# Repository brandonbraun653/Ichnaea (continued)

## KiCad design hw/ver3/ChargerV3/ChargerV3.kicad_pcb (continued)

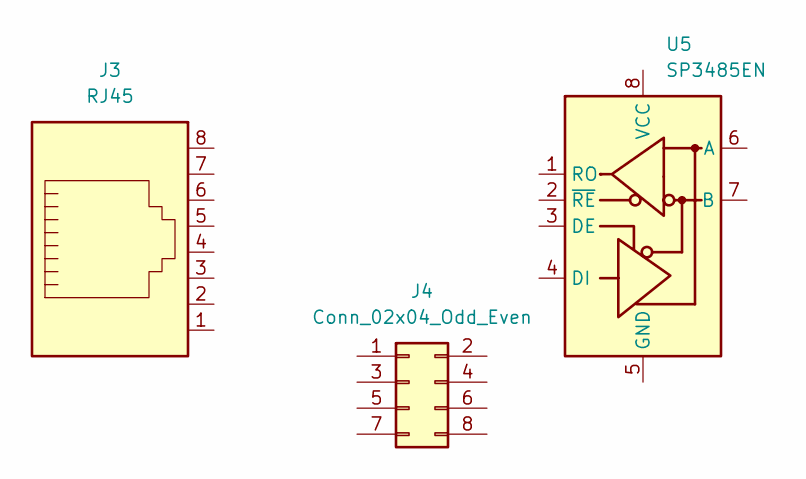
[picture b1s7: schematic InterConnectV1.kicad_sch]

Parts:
J3: RJ45
J4: Conn_02x04_Odd_Even; PinHeader_2x04_P2.54mm_Vertical
U5: SP3485EN; SOIC-8_3.9x4.9mm_P1.27mm

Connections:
+3.3V: U5.8 (VCC); also elsewhere on the board
/ControlStage/InterConnectV1/IC_DATA_IN: U5.4 (DI); also elsewhere on the board
/ControlStage/InterConnectV1/IC_DATA_OUT: U5.1 (RO); also elsewhere on the board
/ControlStage/InterConnectV1/IC_LED_IN_G: J3.9; also elsewhere on the board
/ControlStage/InterConnectV1/IC_LED_IN_Y: J3.11, U5.2 (~RE), U5.3 (DE); also elsewhere on the board
GND: J3.7, J3.8, J3.SH, U5.5 (GND); also elsewhere on the board
IO_DATA_A1: J3.1, J4.1; also elsewhere on the board
IO_DATA_A2: J3.3, J4.3; also elsewhere on the board
IO_DATA_B1: J3.2, J4.5; also elsewhere on the board
IO_DATA_B2: J3.6, J4.7; also elsewhere on the board
IO_PWR_+48V: J3.4, J3.5; also elsewhere on the board
unnamed 86: J3.10; also elsewhere on the board
unnamed 87: J3.12; also elsewhere on the board
unnamed 88: J4.6, J4.8, U5.7 (B); also elsewhere on the board
unnamed 97: J4.2, J4.4, U5.6 (A); also elsewhere on the board

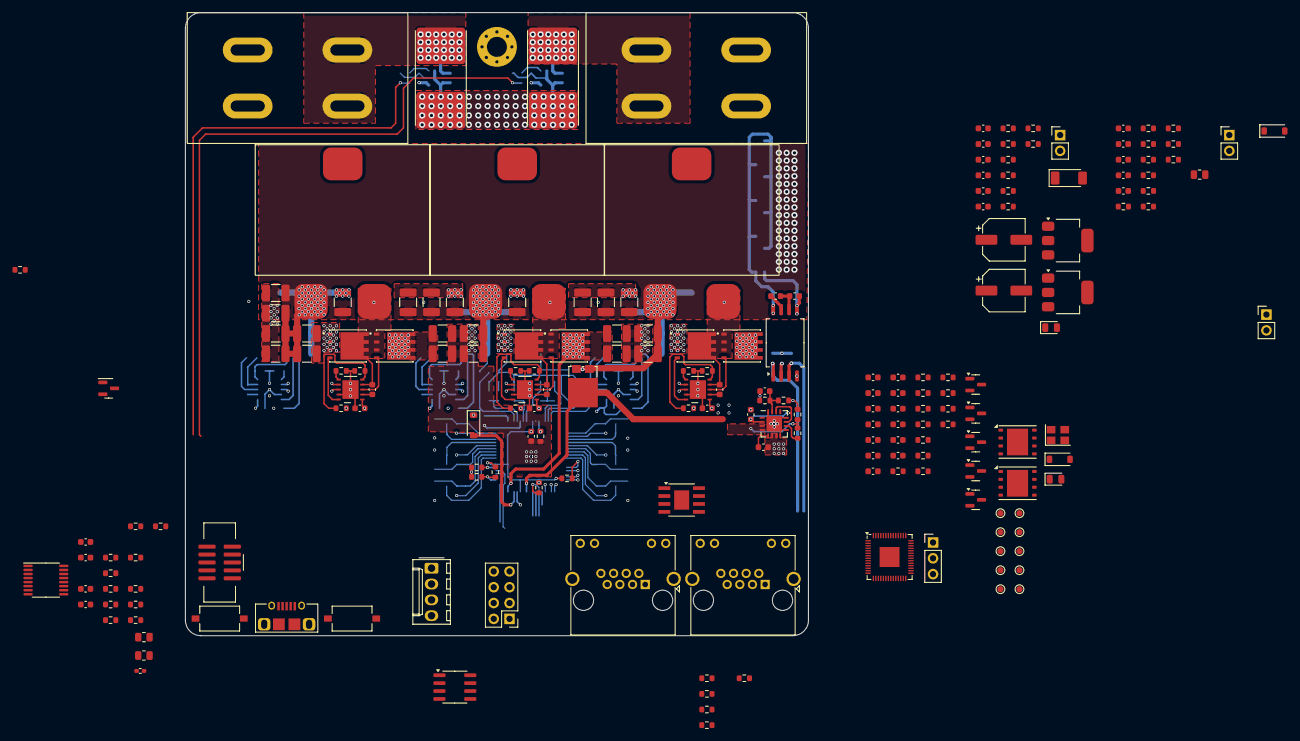
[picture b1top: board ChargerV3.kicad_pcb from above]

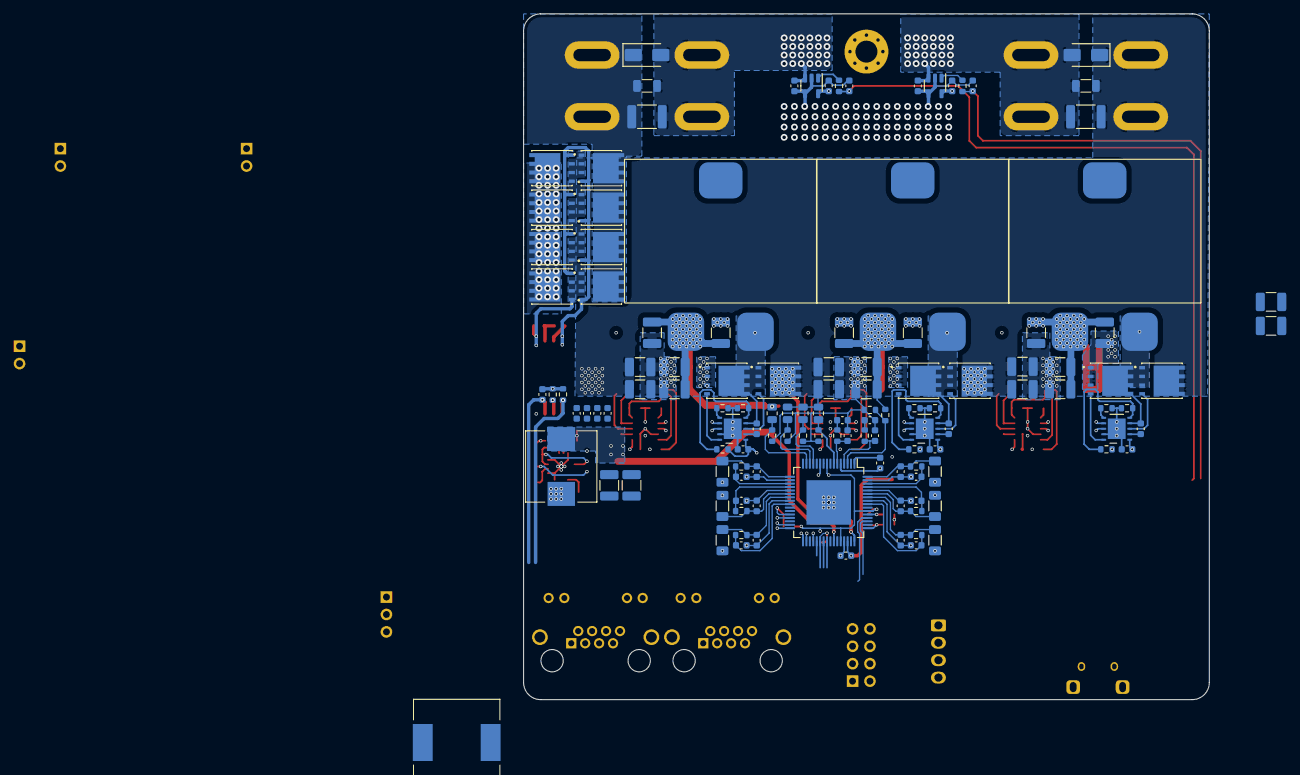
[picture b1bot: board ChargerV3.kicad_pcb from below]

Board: 4 copper layers, 100.0 x 100.0 mm, 322 parts (125 on the bottom side), 186 nets.

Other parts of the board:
C109, C120, C130: 10uF; C_0603_1608Metric
C110, C112, C113: 100nF; C_0603_1608Metric
C116, C117: 100uF-16v; CP_Elec_6.3x5.4
D4: PGOOD; LED_0805_2012Metric
D6: STPS360AF; D_SOD-128
J6: DataOUT; RJ45_Amphenol_RJHSE538X
J10: TermEnable; PinHeader_1x02_P2.54mm_Vertical
L1: 15uH; L_12x12mm_H4.5mm
R5, R25, R58, R59: 3k; R_0603_1608Metric
R63: 120; R_0603_1608Metric
R64: 47k; R_0603_1608Metric
R65, R67, R93, R94, R106: 10k; R_0603_1608Metric
R105: 88.7k; R_0603_1608Metric
U13: ST1S14PHR; TI_SO-PowerPAD-8
U16: AMS1117-5.0; SOT-223-3_TabPin2
U23: AMS1117-3.3; SOT-223-3_TabPin2

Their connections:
+3.3V: C113.1, C130.1, U23.2 (VO); also elsewhere on the board
+5V: C120.1, R5.2, R25.2, R58.2, R59.2, U16.2 (VO), U23.3 (VI); also elsewhere on the board
/ControlStage/InterConnectV1/IC_DATA_IN: R65.2; also elsewhere on the board
/ControlStage/InterConnectV1/IC_DATA_OUT: R93.2; also elsewhere on the board
/ControlStage/InterConnectV1/IC_LED_IN_G: J6.9; also elsewhere on the board
/ControlStage/InterConnectV1/IC_LED_IN_Y: J6.11, R67.2; also elsewhere on the board
/ControlStage/InterConnectV1/IC_PWR_12V: C116.1, C117.1, L1.1, R105.1, R106.2, U16.3 (VI); also elsewhere on the board
GND: C109.2, C110.2, C113.2, C116.2, C117.2, C120.2, C130.2, D6.2 (A), J6.7, J6.8, J6.SH, R65.1, R67.1, R93.1, R94.1, R106.1, U13.3 (~EN1), U13.6 (GND), U13.9 (PADGND), U16.1 (GND), U23.1 (GND); also elsewhere on the board
IO_DATA_A1: J6.1; also elsewhere on the board
IO_DATA_A2: J6.3; also elsewhere on the board
IO_DATA_B1: J6.2; also elsewhere on the board
IO_DATA_B2: J6.6; also elsewhere on the board
IO_PWR_+48V: C109.1, C110.1, J6.4, J6.5, R64.1, U13.5 (EN2), U13.7 (VIN); also elsewhere on the board
unnamed: D4.2 (A), R64.2
unnamed: D4.1 (K), U13.2 (PG)
unnamed: C112.1, D6.1 (K), L1.2, U13.8 (SW)
unnamed 86: R5.1; also elsewhere on the board
unnamed 87: R25.1; also elsewhere on the board
unnamed 88: R63.1; also elsewhere on the board
unnamed: J6.10, R58.1
unnamed: J6.12, R59.1
unnamed 97: J10.1; also elsewhere on the board
unnamed: J10.2, R63.2
unnamed: C112.2, U13.1 (BOOT)
unnamed: R94.2, R105.2, U13.4 (FB)

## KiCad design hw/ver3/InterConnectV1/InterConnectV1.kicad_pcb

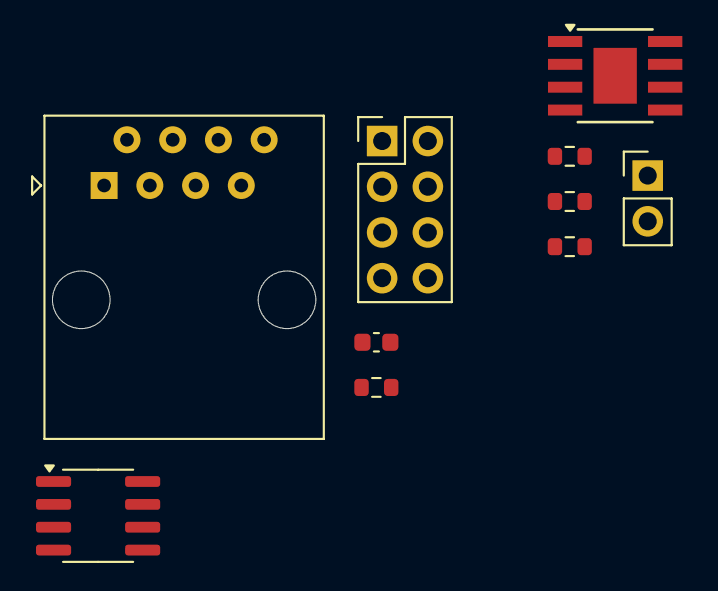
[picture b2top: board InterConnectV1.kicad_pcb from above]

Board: 2 copper layers, 10 parts (0 on the bottom side), 13 nets, no tracks yet.

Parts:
C1: 100nF; C_0603_1608Metric
J1: RJ45; RJ45_Amphenol_54602-x08_Horizontal
J2: DataBusSelector; PinHeader_2x04_P2.54mm_Vertical
J3: TermEnable; PinHeader_1x02_P2.54mm_Vertical
R1, R2, R3: 10k; R_0603_1608Metric
R4: 120; R_0603_1608Metric
U1: SP3485EN; SOIC-8_3.9x4.9mm_P1.27mm
U2: ST1S14PHR; TI_SO-PowerPAD-8

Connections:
+5V: C1.1, U1.8 (VCC)
GND: C1.2, J1.7, J1.8, R1.1, R2.1, R3.1, U1.5 (GND)
INTERCONNECT_DATA_IN: R1.2, U1.4 (DI)
INTERCONNECT_DATA_OUT: R3.2, U1.1 (RO)
INTERCONNECT_RTX_EN: R2.2, U1.2 (~RE), U1.3 (DE)
IO_DATA_A1: J1.1, J2.1
IO_DATA_A2: J1.3, J2.3
IO_DATA_B1: J1.2, J2.5
IO_DATA_B2: J1.6, J2.7
IO_PWR_+48V: J1.4, J1.5
unnamed: J2.2, J2.4, J3.1, U1.6 (A)
unnamed: J2.6, J2.8, R4.1, U1.7 (B)
unnamed: J3.2, R4.2

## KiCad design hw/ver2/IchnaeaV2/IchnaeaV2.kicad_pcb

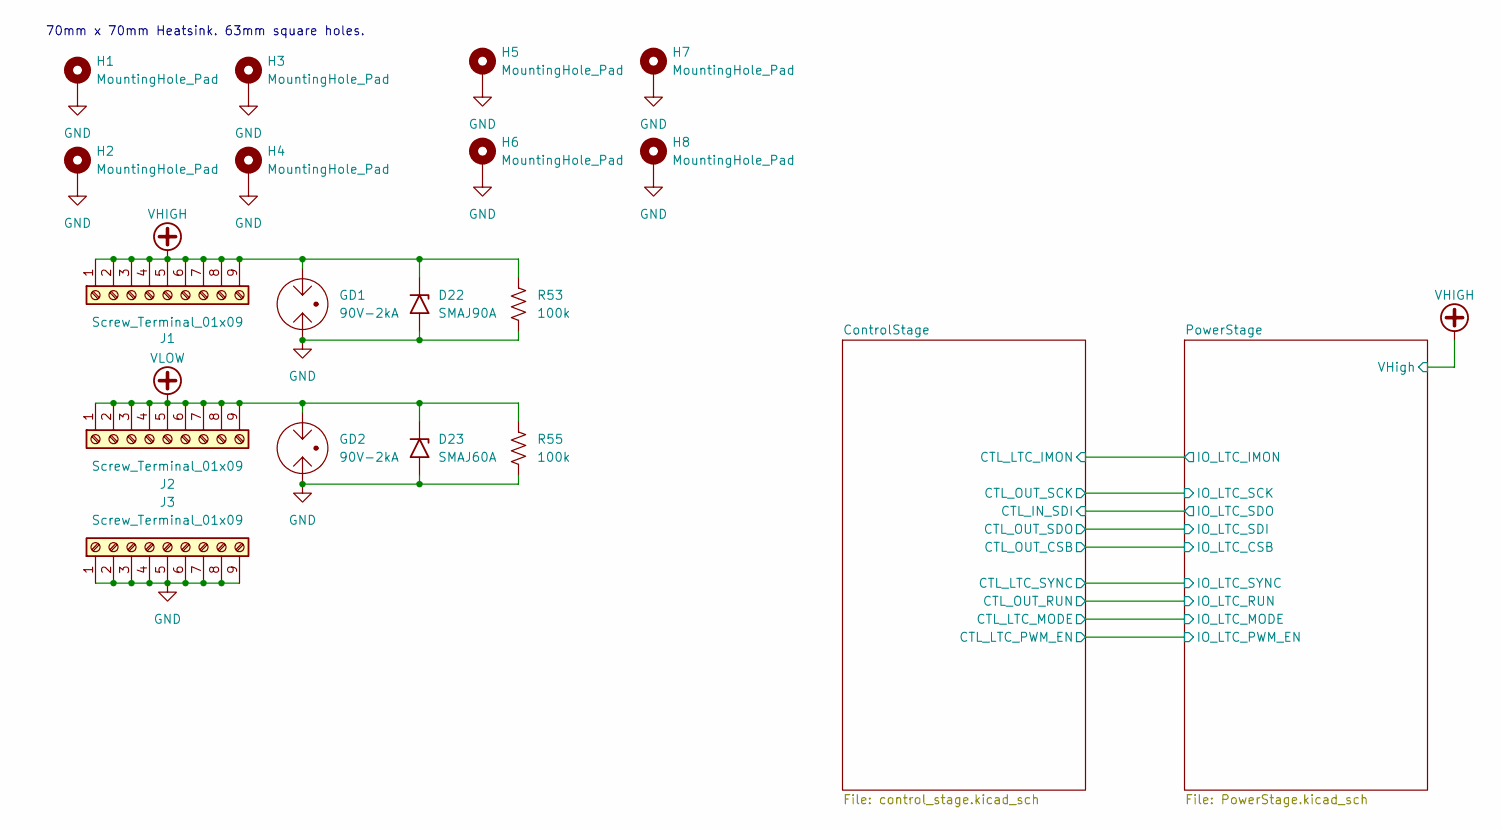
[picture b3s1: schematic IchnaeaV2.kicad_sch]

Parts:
D22: SMAJ90A; D_SMA; LCSC C2989723
D23: SMAJ60A; D_SMA; LCSC C707480
GD1, GD2: 90V-2kA; Fuse_1812_4532Metric_Pad1.30x3.40mm_HandSolder; LCSC C78323
H1, H2, H3, H4, H5, H6, H7, H8: MountingHole_Pad; MountingHole_3.2mm_M3_Pad_Via; Digikey N/A
J1, J2, J3: Screw_Terminal_01x09; CONN_74651195R_WRE; Digikey 732-74651195RCT-ND
R53, R55: 100k; R_1206_3216Metric; LCSC C17900

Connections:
GND: D22.2 (A2), D23.2 (A2), GD1.1, GD2.1, H1.1, H2.1, H3.1, H4.1, H5.1, H6.1, H7.1, H8.1, J3.1, J3.2, J3.3, J3.4, J3.5, J3.6, J3.7, J3.8, J3.9, R53.2, R55.2; also elsewhere on the board
VHIGH: D22.1 (A1), GD1.2, J1.1, J1.2, J1.3, J1.4, J1.5, J1.6, J1.7, J1.8, J1.9, R53.1; also elsewhere on the board
VLOW: D23.1 (A1), GD2.2, J2.1, J2.2, J2.3, J2.4, J2.5, J2.6, J2.7, J2.8, J2.9, R55.1; also elsewhere on the board

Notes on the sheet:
70mm x 70mm Heatsink. 63mm square holes.

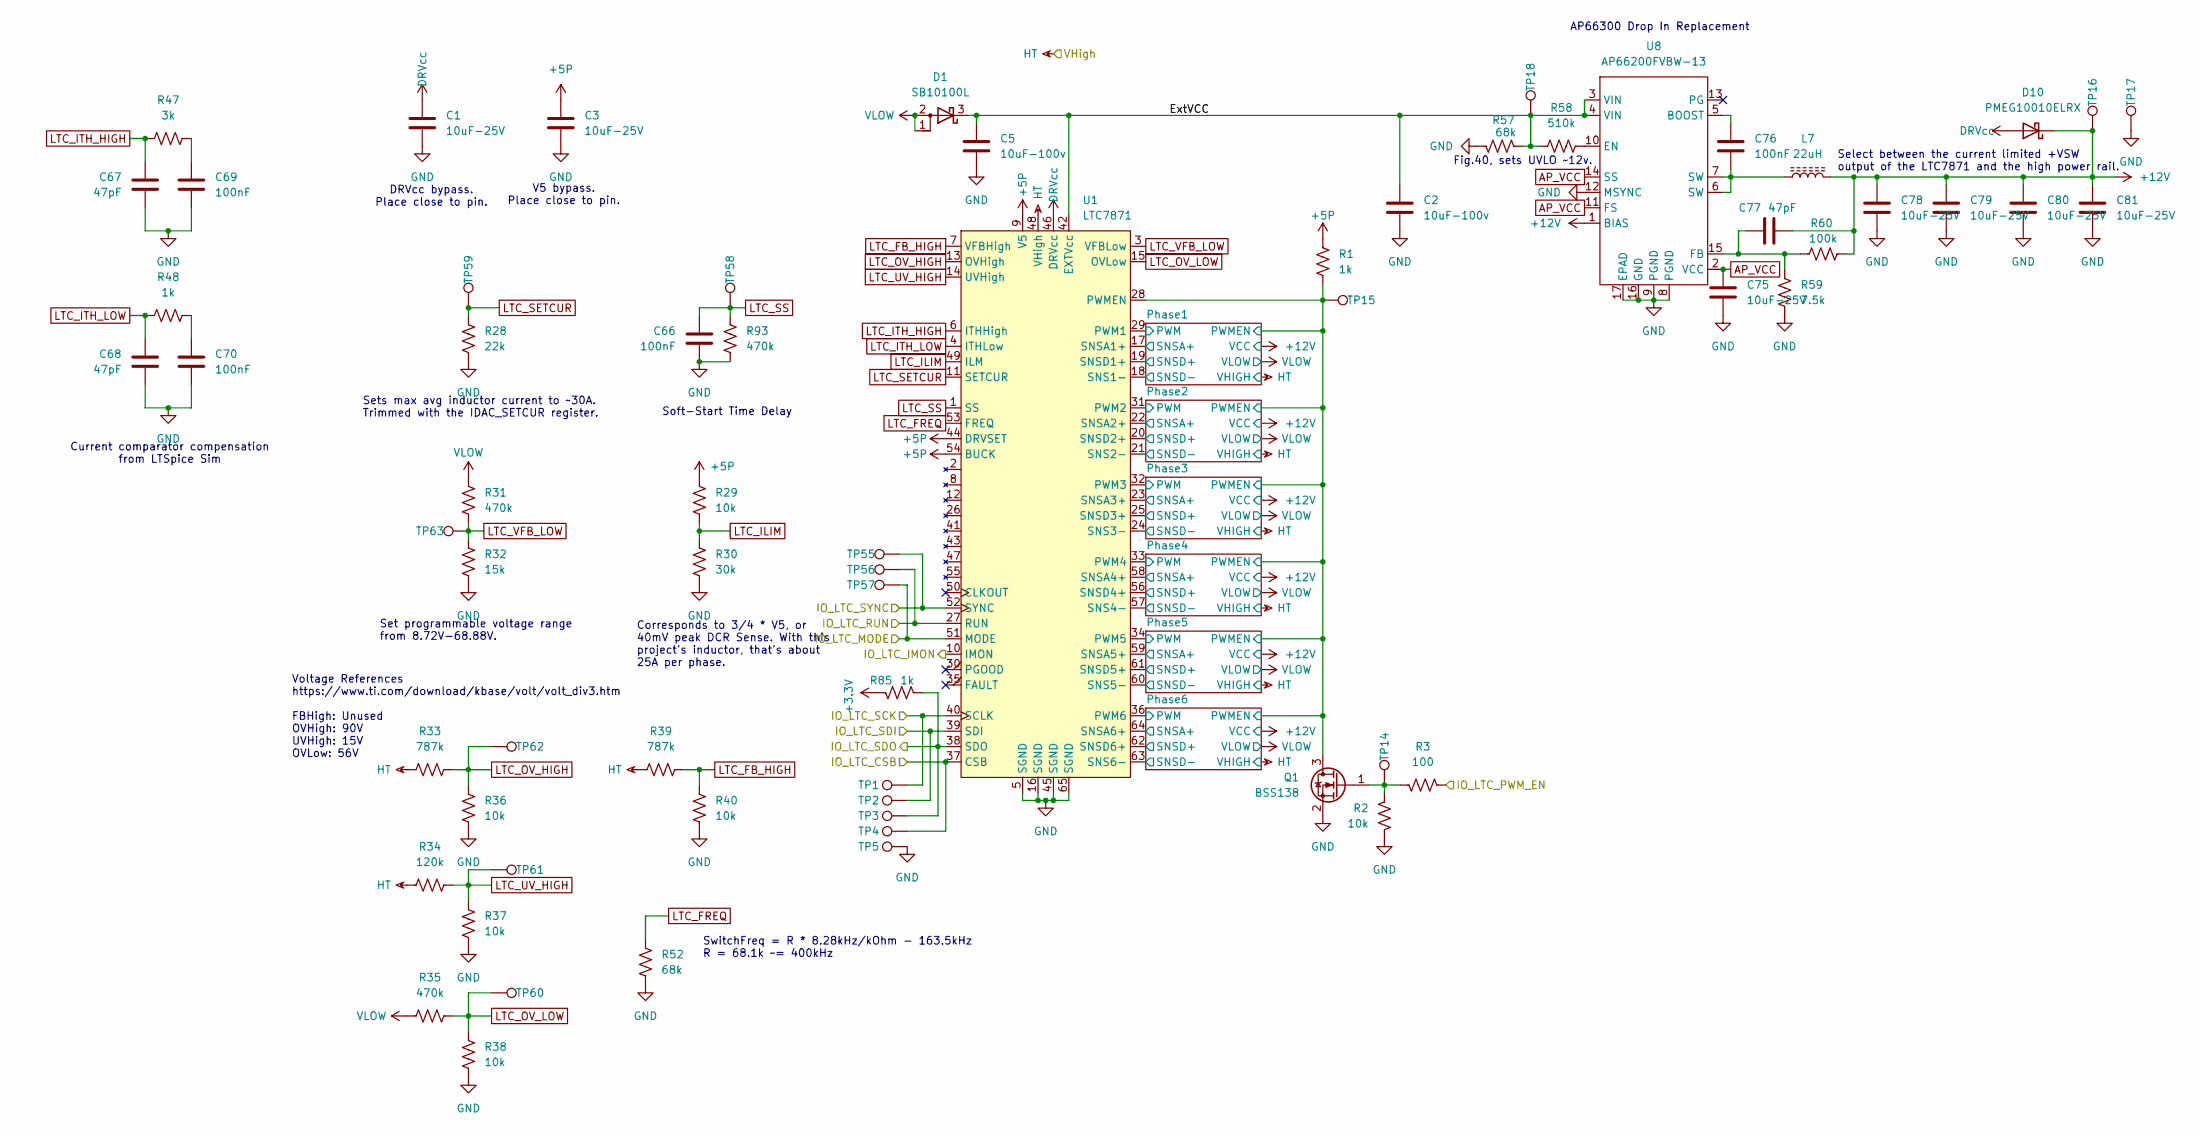
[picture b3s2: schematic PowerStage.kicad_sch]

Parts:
C1: 10uF-25V; C_0603_1608Metric; Voltage 25; Digikey N/A
C2, C5: 10uF-100v; C_1210_3225Metric_Pad1.33x2.70mm_HandSolder; Digikey 445-CGA6P1X7R1N106M250ACCT-ND
C3, C75, C78, C79, C80, C81: 10uF-25V; C_0603_1608Metric; Digikey N/A
C66, C69, C70, C76: 100nF; C_0603_1608Metric; LCSC C14663
C67, C68, C77: 47pF; C_0603_1608Metric; LCSC C1671
D1: SB10100L; TO-277A; LCSC C113946
D10: PMEG10010ELRX; D_SOD-123; LCSC C179426
L7: 22uH; L_Wuerth_HCI-1040; Digikey N/A
Q1: BSS138; SOT-23; Digikey 5272-BSS138CT-ND
R1, R48, R85: 1k; R_0603_1608Metric; Digikey N/A
R2, R29, R36, R37, R38, R40: 10k; R_0603_1608Metric; LCSC C25804
R3: 100; R_0603_1608Metric; Digikey N/A
R28: 22k; R_0603_1608Metric; LCSC C31850
R30: 30k; R_0603_1608Metric; Digikey N/A
R31, R35: 470k; R_0805_2012Metric; LCSC C17709
R32: 15k; R_0603_1608Metric; LCSC C22809
R33, R39: 787k; R_0805_2012Metric; Digikey P787KHCT-ND
R34: 120k; R_0603_1608Metric; Digikey N/A
R47: 3k; R_0603_1608Metric; Digikey N/A
R52: 68k; R_0603_1608Metric; Digikey N/A
R57: 68k; R_0603_1608Metric; LCSC C23231
R58: 510k; R_0603_1608Metric; LCSC C23192
R59: 7.5k; R_0603_1608Metric; LCSC C23234
R60: 100k; R_0603_1608Metric; LCSC C25803
R93: 470k; R_0805_2012Metric; Digikey N/A
TP1, TP2, TP3, TP4, TP5, TP14, TP15, TP16, TP17, TP18, TP55, TP56, TP57, TP58, TP59, TP60, TP61, TP62, TP63: TestPoint; TestPoint_Pad_D1.0mm
U1: LTC7871; LQFP-64-1EP_10x10mm_P0.5mm_EP6.5x6.5mm; Digikey 505-LTC7871ELWE#PBF-ND
U8: AP66200FVBW-13; QFN-16-1EP_4x4mm_P0.65mm_EP2.5x2.5mm; Digikey 31-AP66200FVBW-13CT-ND

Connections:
+3.3V: R85.2; also elsewhere on the board
+5P: C3.1, R1.2, R29.2, U1.9 (V5), U1.44 (DRVSET), U1.54 (BUCK)
+12V: C77.2, C78.1, C79.1, C80.1, C81.1, D10.1 (K), L7.2, R60.2, TP16.1, U8.1 (BIAS); also elsewhere on the board
/ControlStage/CTL_LTC_IMON: U1.10 (IMON); also elsewhere on the board
/ControlStage/CTL_LTC_MODE: TP57.1, U1.51 (MODE); also elsewhere on the board
/ControlStage/CTL_LTC_PWM_EN: R3.2; also elsewhere on the board
/ControlStage/CTL_LTC_SYNC: TP55.1, U1.52 (SYNC); also elsewhere on the board
/ControlStage/CTL_OUT_RUN: TP56.1, U1.27 (RUN); also elsewhere on the board
/ControlStage/SPI1_CSn: TP4.1, U1.37 (CSB); also elsewhere on the board
/ControlStage/SPI1_RX: R85.1, TP3.1, U1.38 (SDO); also elsewhere on the board
/ControlStage/SPI1_SCK: TP1.1, U1.40 (SCLK); also elsewhere on the board
/ControlStage/SPI1_TX: TP2.1, U1.39 (SDI); also elsewhere on the board
/PowerStage/ExtVCC: C2.1, C5.1, D1.3 (K), R57.1, R58.1, TP18.1, U1.42 (EXTVcc), U8.3 (VIN), U8.4 (VIN)
/PowerStage/Phase1/PWM: U1.29 (PWM1); also elsewhere on the board
/PowerStage/Phase1/PWMEN: Q1.3 (D), R1.1, TP15.1, U1.28 (PWMEN); also elsewhere on the board
/PowerStage/Phase1/SNSA+: U1.17 (SNSA1+); also elsewhere on the board
/PowerStage/Phase1/SNSD+: U1.19 (SNSD1+); also elsewhere on the board
/PowerStage/Phase2/PWM: U1.31 (PWM2); also elsewhere on the board
/PowerStage/Phase2/SNSA+: U1.22 (SNSA2+); also elsewhere on the board
/PowerStage/Phase2/SNSD+: U1.20 (SNSD2+); also elsewhere on the board
/PowerStage/Phase3/PWM: U1.32 (PWM3); also elsewhere on the board
/PowerStage/Phase3/SNSA+: U1.23 (SNSA3+); also elsewhere on the board
/PowerStage/Phase3/SNSD+: U1.25 (SNSD3+); also elsewhere on the board
/PowerStage/Phase4/PWM: U1.33 (PWM4); also elsewhere on the board
/PowerStage/Phase4/SNSA+: U1.58 (SNSA4+); also elsewhere on the board
/PowerStage/Phase4/SNSD+: U1.56 (SNSD4+); also elsewhere on the board
/PowerStage/Phase5/PWM: U1.34 (PWM5); also elsewhere on the board
/PowerStage/Phase5/SNSA+: U1.59 (SNSA5+); also elsewhere on the board
/PowerStage/Phase5/SNSD+: U1.61 (SNSD5+); also elsewhere on the board
/PowerStage/Phase6/PWM: U1.36 (PWM6); also elsewhere on the board
/PowerStage/Phase6/SNSA+: U1.64 (SNSA6+); also elsewhere on the board
/PowerStage/Phase6/SNSD+: U1.62 (SNSD6+); also elsewhere on the board
AP_VCC: C75.1, U8.2 (VCC), U8.11 (FS), U8.14 (SS)
DRVcc: C1.1, D10.2 (A), U1.46 (DRVcc)
GND: C1.2, C2.2, C3.2, C5.2, C66.2, C67.2, C68.2, C69.2, C70.2, C75.2, C78.2, C79.2, C80.2, C81.2, Q1.2 (S), R2.1, R28.1, R30.1, R32.1, R36.1, R37.1, R38.1, R40.1, R52.1, R57.2, R59.2, R93.1, TP5.1, TP17.1, U1.5 (SGND), U1.16 (SGND), U1.45 (SGND), U1.65 (SGND), U8.8 (PGND), U8.9 (PGND), U8.12 (MSYNC), U8.16 (GND), U8.17 (EPAD); also elsewhere on the board
LTC_FB_HIGH: R39.2, R40.2, U1.7 (VFBHigh)
LTC_FREQ: R52.2, U1.53 (FREQ)
LTC_ILIM: R29.1, R30.2, U1.49 (ILM)
LTC_ITH_HIGH: C67.1, R47.2, U1.6 (ITHHigh)
LTC_ITH_LOW: C68.1, R48.2, U1.4 (ITHLow)
LTC_OV_HIGH: R33.2, R36.2, TP62.1, U1.13 (OVHigh)
LTC_OV_LOW: R35.2, R38.2, TP60.1, U1.15 (OVLow)
LTC_SETCUR: R28.2, TP59.1, U1.11 (SETCUR)
LTC_SS: C66.1, R93.2, TP58.1, U1.1 (SS)
LTC_UV_HIGH: R34.2, R37.2, TP61.1, U1.14 (UVHigh)
LTC_VFB_LOW: R31.1, R32.2, TP63.1, U1.3 (VFBLow)
unnamed: C69.1, R47.1
unnamed: C70.1, R48.1
unnamed: C76.2, L7.1, U8.6 (SW), U8.7 (SW)
unnamed: Q1.1 (G), R2.2, R3.1, TP14.1
unnamed: C76.1, U8.5 (BOOST)
unnamed: R58.2, U8.10 (EN)
unnamed: C77.1, R59.1, R60.1, U8.15 (FB)
VHIGH: R33.1, R34.1, R39.1, U1.48 (VHigh); also elsewhere on the board
VLOW: D1.1 (A), D1.2 (A), R31.2, R35.1, U1.18 (SNS1-), U1.21 (SNS2-), U1.24 (SNS3-), U1.57 (SNS4-), U1.60 (SNS5-), U1.63 (SNS6-); also elsewhere on the board

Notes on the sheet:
SwitchFreq = R * 8.28kHz/kOhm - 163.5kHz R = 68.1k ~= 400kHz
Fig.40, sets UVLO ~12v.
V5 bypass. Place close to pin.
Sets max avg inductor current to ~30A. Trimmed with the IDAC_SETCUR register.
Corresponds to 3/4 * V5, or 40mV peak DCR Sense. With this project's inductor, that's about 25A per phase.
Select between the current limited +VSW output of the LTC7871 and the high power rail.
Set programmable voltage range from 8.72V-68.88V.
Current comparator compensation from LTSpice Sim
Soft-Start Time Delay
AP66300 Drop In Replacement
Voltage References https://www.ti.com/download/kbase/volt/volt_div3.htm FBHigh: Unused OVHigh: 90V UVHigh: 15V OVLow: 56V
DRVcc bypass. Place close to pin.

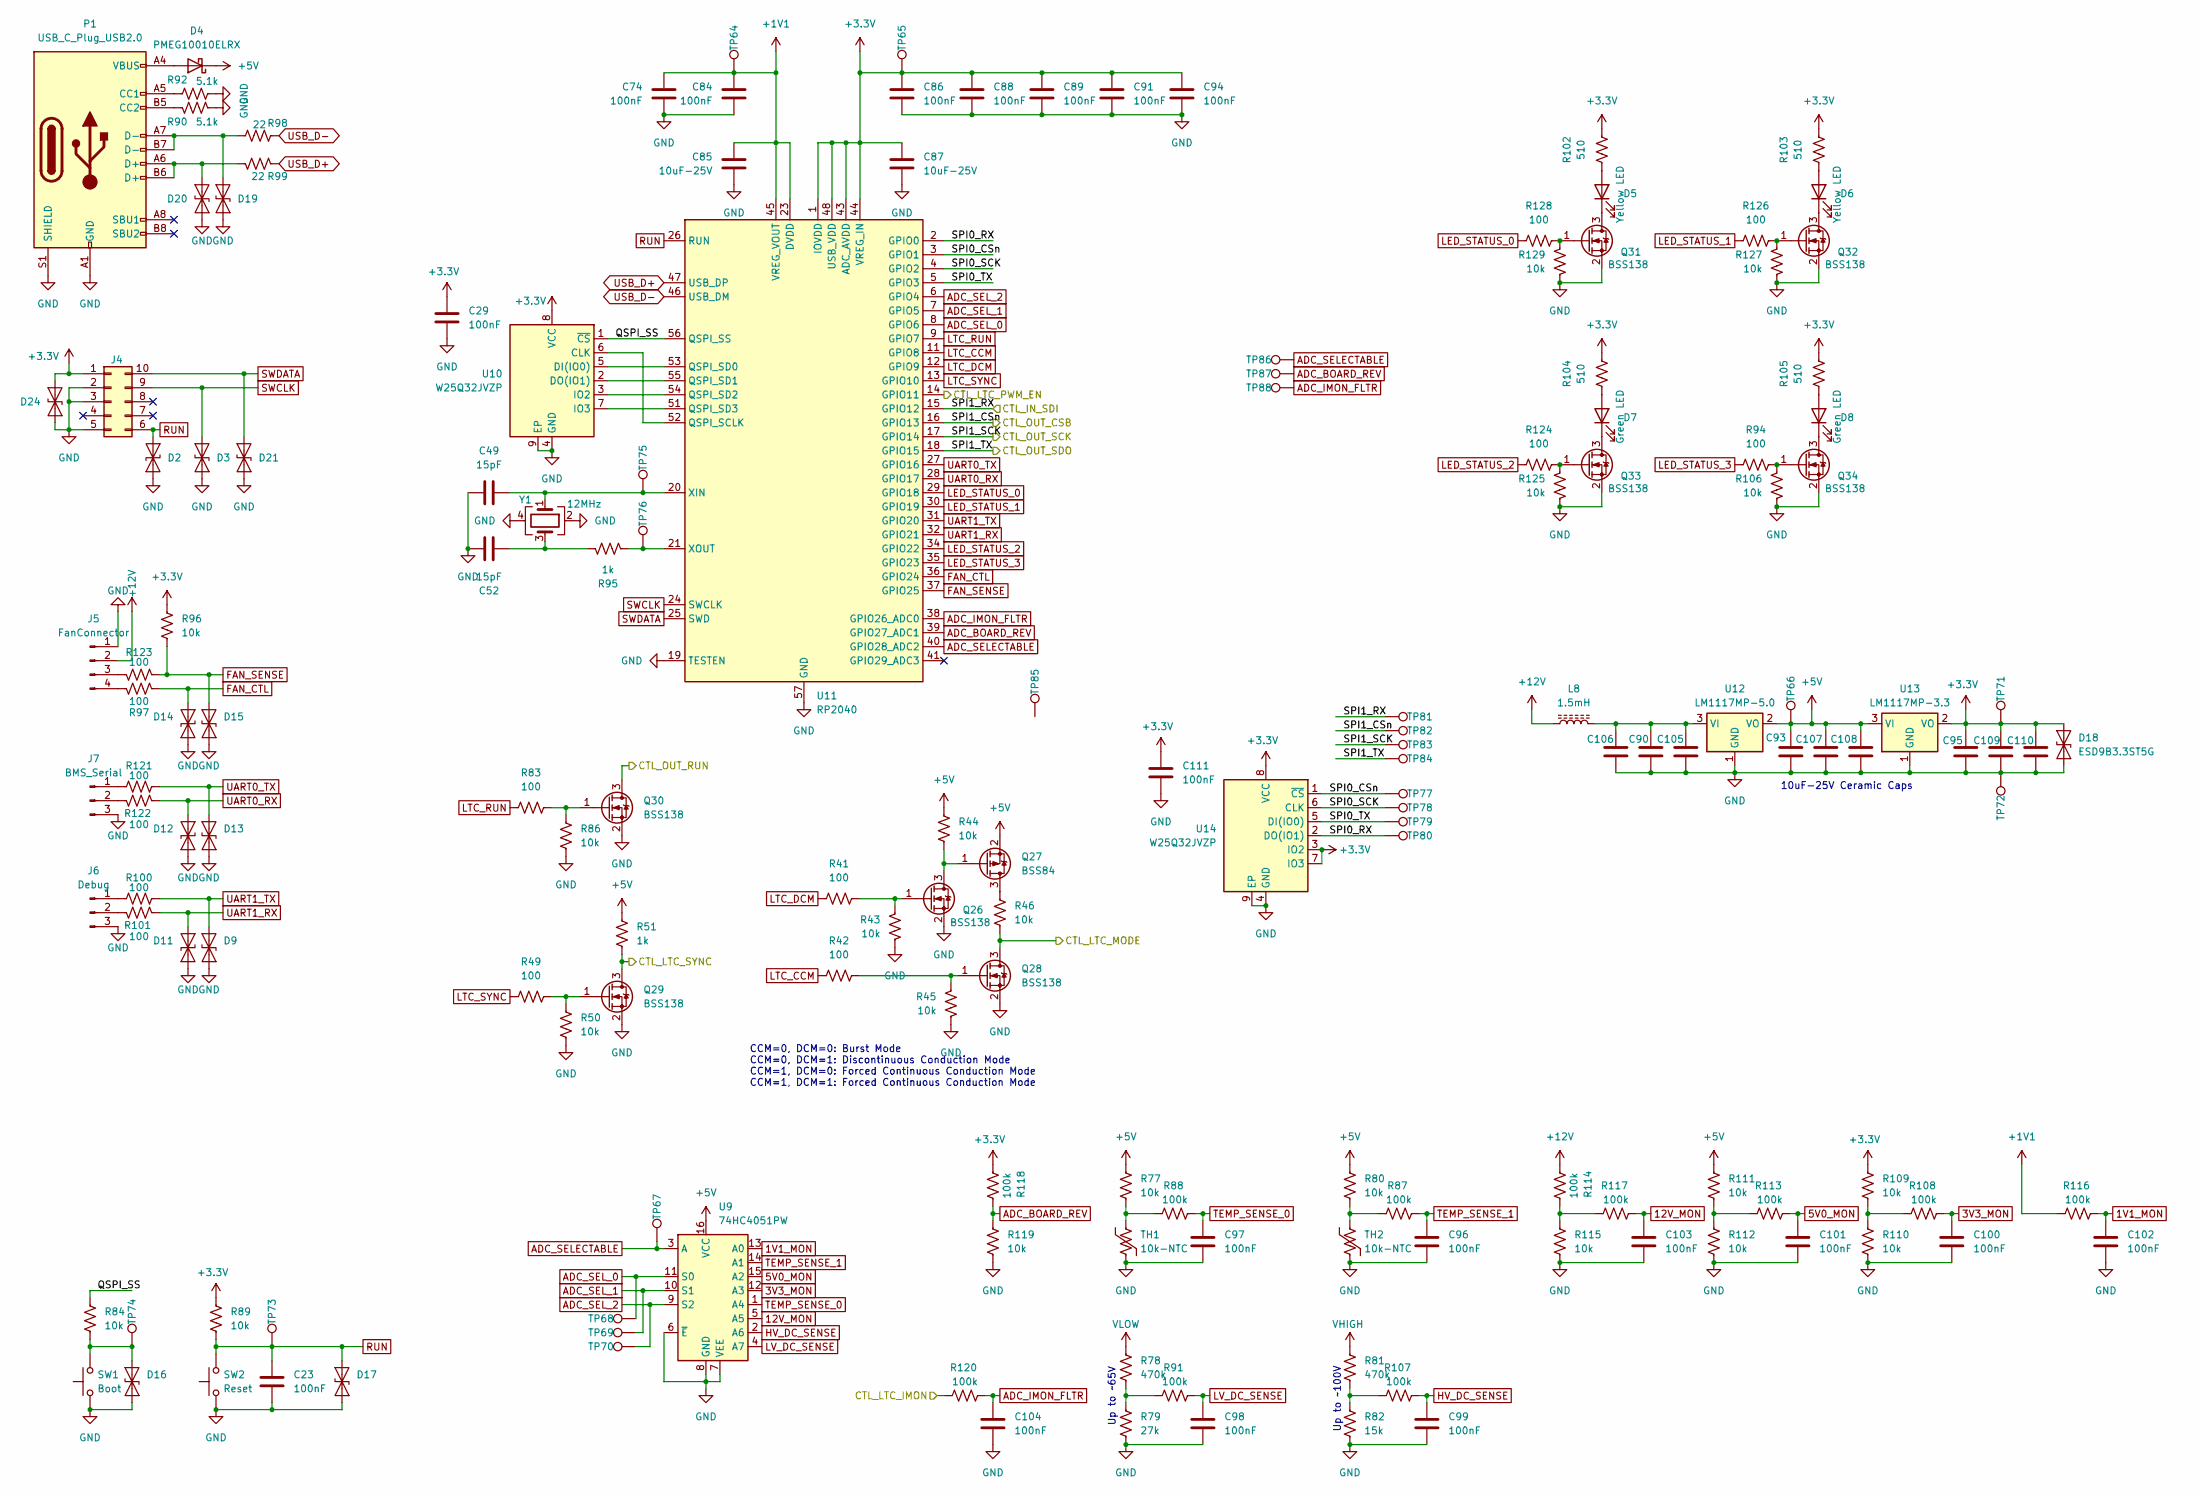
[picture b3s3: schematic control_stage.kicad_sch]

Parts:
C23, C29, C74, C84, C86, C88, C89, C91, C94, C96, C97, C98, C99, C100, C101, C102, C103, C104, C111: 100nF; C_0603_1608Metric; LCSC C14663
C49, C52: 15pF; C_0603_1608Metric; Digikey N/A
C85, C87, C90, C93, C95, C105, C106, C107, C108, C109, C110: 10uF-25V; C_0603_1608Metric; Digikey N/A
D2, D3, D19, D20, D21, D24: ESD9B5.0ST5G; D_SOD-923; LCSC C3021104
D4: PMEG10010ELRX; D_SOD-123; LCSC C179426
D5, D6: Yellow LED; LED_0805_2012Metric; LCSC C2296
D7, D8: Green LED; LED_0805_2012Metric; LCSC C2297
D9, D11, D12, D13, D14, D15, D16, D17, D18: ESD9B3.3ST5G; D_SOD-923; LCSC C96512
J4: JTAG_2x05_P1_27mm_Shrouded_SMD; Digikey 1175-1629-ND
J5: FanConnector; Molex_KK-254_AE-6410-04A_1x04_P2.54mm_Vertical; Digikey WM4330-ND
J6: Debug; PinHeader_1x03_P2.54mm_Vertical; Digikey N/A
J7: BMS_Serial; PinHeader_1x03_P2.54mm_Vertical; Digikey N/A
L8: 1.5mH; L_Changjiang_FNR6045S; LCSC C168103
P1: USB_C_Plug_USB2.0; USB_C_Receptacle_GCT_USB4085; Digikey 2073-USB4085-GF-ACT-ND
Q26, Q28, Q29, Q30, Q31, Q32, Q33, Q34: BSS138; SOT-23; Digikey 5272-BSS138CT-ND
Q27: BSS84; SOT-23; Digikey 5272-BSS84CT-ND
R41, R42, R49, R83, R94, R97, R100, R101, R121, R122, R123, R124, R126, R128: 100; R_0603_1608Metric; Digikey N/A
R43, R44, R45, R46, R50, R77, R80, R84, R86, R89, R96, R106, R109, R110, R111, R112, R115, R119, R125, R127, R129: 10k; R_0603_1608Metric; LCSC C25804
R51: 1k; R_0603_1608Metric; LCSC C21190
R78: 470k; R_0805_2012Metric; Digikey N/A
R79: 27k; R_0603_1608Metric; Digikey N/A
R81: 470k; R_0805_2012Metric; LCSC C17709
R82: 15k; R_0603_1608Metric; Digikey N/A
R87, R88, R91, R107, R108, R113, R114, R116, R117, R118, R120: 100k; R_0603_1608Metric; LCSC C25803
R90, R92: 5.1k; R_0603_1608Metric; LCSC C23186
R95: 1k; R_0603_1608Metric; Digikey N/A
R98, R99: 22; R_0603_1608Metric; LCSC C23345
R102, R103, R104, R105: 510; R_0603_1608Metric; Digikey N/A
SW1: Boot; SW_SPST_EVQP2; Digikey P11081SCT-ND
SW2: Reset; SW_SPST_EVQP2; Digikey P11081SCT-ND
TH1, TH2: 10k-NTC; R_0402_1005Metric_Pad0.72x0.64mm_HandSolder; Digikey 445-2550-1-ND
TP64, TP65, TP66, TP67, TP68, TP69, TP70, TP71, TP72, TP73, TP74, TP75, TP76, TP77, TP78, TP79, TP80, TP81, TP82, TP83, TP84, TP85, TP86, TP87, TP88: TestPoint; TestPoint_Pad_D1.0mm
U9: 74HC4051PW; TSSOP-16_4.4x5mm_P0.65mm; Digikey 1727-3064-1-ND
U10, U14: W25Q32JVZP; WSON-8-1EP_6x5mm_P1.27mm_EP3.4x4.3mm; Digikey W25Q32JVZPIQ-ND
U11: RP2040; QFN-56-1EP_7x7mm_P0.4mm_EP3.2x3.2mm; Digikey 2648-SC0914(13)CT-ND
U12: LM1117MP-5.0; SOT-223-3_TabPin2; LCSC C6187
U13: LM1117MP-3.3; SOT-223-3_TabPin2; Digikey N/A
Y1: 12MHz; Crystal_SMD_3225-4Pin_3.2x2.5mm; Digikey XC2613CT-ND

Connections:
1V1_MON: C102.1, R116.2, U9.13 (A0)
3V3_MON: C100.1, R108.2, U9.12 (A3)
5V0_MON: C101.1, R113.2, U9.15 (A2)
12V_MON: C103.1, R117.2, U9.5 (A5)
+1V1: C74.1, C84.1, C85.1, R116.1, TP64.1, U11.23 (DVDD), U11.45 (VREG_VOUT), U11.50 (DVDD)
+3.3V: C29.1, C86.1, C87.1, C88.1, C89.1, C91.1, C94.1, C95.1, C109.1, C110.1, C111.1, D18.2 (A2), D24.1 (A1), J4.1, R89.2, R96.2, R102.1, R103.1, R104.1, R105.1, R109.2, R118.1, TP65.1, TP71.1, U10.8 (VCC), U11.1 (IOVDD), U11.10 (IOVDD), U11.22 (IOVDD), U11.33 (IOVDD), U11.42 (IOVDD), U11.43 (ADC_AVDD), U11.44 (VREG_IN), U11.48 (USB_VDD), U11.49 (IOVDD), U13.2 (VO), U14.3 (IO2), U14.7 (IO3), U14.8 (VCC); also elsewhere on the board
+5V: C93.1, C107.1, C108.1, D4.1 (K), Q27.2 (S), R44.2, R51.2, R77.2, R80.2, R111.2, TP66.1, U9.16 (VCC), U12.2 (VO), U13.3 (VI)
+12V: J5.2, L8.1, R114.1; also elsewhere on the board
/ControlStage/CTL_LTC_IMON: R120.1; also elsewhere on the board
/ControlStage/CTL_LTC_MODE: Q28.3 (D), R46.2; also elsewhere on the board
/ControlStage/CTL_LTC_PWM_EN: U11.14 (GPIO11); also elsewhere on the board
/ControlStage/CTL_LTC_SYNC: Q29.3 (D), R51.1; also elsewhere on the board
/ControlStage/CTL_OUT_RUN: Q30.3 (D); also elsewhere on the board
/ControlStage/QSPI_SS: R84.2, U10.1 (~CS), U11.56 (QSPI_SS)
/ControlStage/SPI0_CSn: TP77.1, U11.3 (GPIO1), U14.1 (~CS)
/ControlStage/SPI0_RX: TP80.1, U11.2 (GPIO0), U14.2 (DO(IO1))
/ControlStage/SPI0_SCK: TP78.1, U11.4 (GPIO2), U14.6 (CLK)
/ControlStage/SPI0_TX: TP79.1, U11.5 (GPIO3), U14.5 (DI(IO0))
/ControlStage/SPI1_CSn: TP82.1, U11.16 (GPIO13); also elsewhere on the board
/ControlStage/SPI1_RX: TP81.1, U11.15 (GPIO12); also elsewhere on the board
/ControlStage/SPI1_SCK: TP83.1, U11.17 (GPIO14); also elsewhere on the board
/ControlStage/SPI1_TX: TP84.1, U11.18 (GPIO15); also elsewhere on the board
ADC_BOARD_REV: R118.2, R119.2, TP87.1, U11.39 (GPIO27_ADC1)
ADC_IMON_FLTR: C104.1, R120.2, TP88.1, U11.38 (GPIO26_ADC0)
ADC_SELECTABLE: TP67.1, TP86.1, U9.3 (A), U11.40 (GPIO28_ADC2)
ADC_SEL_0: TP68.1, U9.11 (S0), U11.8 (GPIO6)
ADC_SEL_1: TP69.1, U9.10 (S1), U11.7 (GPIO5)
ADC_SEL_2: TP70.1, U9.9 (S2), U11.6 (GPIO4)
FAN_CTL: D14.2 (A2), R97.2, U11.36 (GPIO24)
FAN_SENSE: D15.2 (A2), R96.1, R123.1, U11.37 (GPIO25)
GND: C23.2, C29.2, C49.1, C52.1, C74.2, C84.2, C85.2, C86.2, C87.2, C88.2, C89.2, C90.2, C91.2, C93.2, C94.2, C95.2, C96.2, C97.2, C98.2, C99.2, C100.2, C101.2, C102.2, C103.2, C104.2, C105.2, C106.2, C107.2, C108.2, C109.2, C110.2, C111.2, D2.2 (A2), D3.2 (A2), D9.1 (A1), D11.1 (A1), D12.1 (A1), D13.1 (A1), D14.1 (A1), D15.1 (A1), D16.1 (A1), D17.1 (A1), D18.1 (A1), D19.2 (A2), D20.2 (A2), D21.2 (A2), D24.2 (A2), J4.2, J4.3, J4.5, J5.1, J6.3, J7.3, P1.A1 (GND), P1.A12 (GND), P1.B1 (GND), P1.B12 (GND), P1.S1 (SHIELD), Q26.2 (S), Q28.2 (S), Q29.2 (S), Q30.2 (S), Q31.2 (S), Q32.2 (S), Q33.2 (S), Q34.2 (S), R43.1, R45.1, R50.1, R79.1, R82.1, R86.1, R90.1, R92.1, R106.1, R110.1, R112.1, R115.1, R119.1, R125.1, R127.1, R129.1, SW1.1, SW2.1, TH1.2, TH2.2, TP72.1, U9.6 (~E), U9.7 (VEE), U9.8 (GND), U10.4 (GND), U10.9 (EP), U11.19 (TESTEN), U11.57 (GND), U12.1 (GND), U13.1 (GND), U14.4 (GND), U14.9 (EP), Y1.2, Y1.4; also elsewhere on the board
HV_DC_SENSE: C99.1, R107.2, U9.2 (A6)
LED_STATUS_0: R128.2, U11.29 (GPIO18)
LED_STATUS_1: R126.2, U11.30 (GPIO19)
LED_STATUS_2: R124.2, U11.34 (GPIO22)
LED_STATUS_3: R94.2, U11.35 (GPIO23)
LTC_CCM: R42.2, U11.11 (GPIO8)
LTC_DCM: R41.2, U11.12 (GPIO9)
LTC_RUN: R83.2, U11.9 (GPIO7)
LTC_SYNC: R49.2, U11.13 (GPIO10)
LV_DC_SENSE: C98.1, R91.2, U9.4 (A7)
unnamed: C52.2, R95.1, Y1.3
unnamed: D4.2 (A), P1.A4 (VBUS), P1.A9 (VBUS), P1.B4 (VBUS), P1.B9 (VBUS)
unnamed: D5.2 (A), R102.2
unnamed: D5.1 (K), Q31.3 (D)
unnamed: D6.2 (A), R103.2
unnamed: D6.1 (K), Q32.3 (D)
unnamed: D7.2 (A), R104.2
unnamed: D7.1 (K), Q33.3 (D)
unnamed: D8.2 (A), R105.2
unnamed: D8.1 (K), Q34.3 (D)
unnamed: D16.2 (A2), R84.1, SW1.2, TP74.1
unnamed: D19.1 (A1), P1.A7 (D-), P1.B7 (D-), R98.2
unnamed: D20.1 (A1), P1.A6 (D+), P1.B6 (D+), R99.2
unnamed: J5.3, R123.2
unnamed: J5.4, R97.1
unnamed: J6.1, R100.1
unnamed: J6.2, R101.1
unnamed: J7.1, R121.1
unnamed: J7.2, R122.1
unnamed: P1.A5 (CC1), R92.2
unnamed: P1.B5 (CC2), R90.2
unnamed: Q26.3 (D), Q27.1 (G), R44.1
unnamed: Q26.1 (G), R41.1, R43.2
unnamed: Q27.3 (D), R46.1
unnamed: Q28.1 (G), R42.1, R45.2
unnamed: Q29.1 (G), R49.1, R50.2
unnamed: Q30.1 (G), R83.1, R86.2
unnamed: Q31.1 (G), R128.1, R129.2
unnamed: Q32.1 (G), R126.1, R127.2
unnamed: Q33.1 (G), R124.1, R125.2
unnamed: Q34.1 (G), R94.1, R106.2
unnamed: R77.1, R88.1, TH1.1
unnamed: R78.1, R79.2, R91.1
unnamed: R80.1, R87.1, TH2.1
unnamed: R81.1, R82.2, R107.1
unnamed: R108.1, R109.1, R110.2
unnamed: R111.1, R112.2, R113.1
unnamed: R114.2, R115.2, R117.1
unnamed: U10.6 (CLK), U11.52 (QSPI_SCLK)
unnamed: U10.5 (DI(IO0)), U11.53 (QSPI_SD0)
unnamed: U10.2 (DO(IO1)), U11.55 (QSPI_SD1)
unnamed: U10.3 (IO2), U11.54 (QSPI_SD2)
unnamed: U10.7 (IO3), U11.51 (QSPI_SD3)
unnamed: C49.2, TP75.1, U11.20 (XIN), Y1.1
unnamed: R95.2, TP76.1, U11.21 (XOUT)
unnamed: C90.1, C105.1, C106.1, L8.2, U12.3 (VI)
RUN: C23.1, D2.1 (A1), D17.2 (A2), J4.6, R89.1, SW2.2, TP73.1, U11.26 (RUN)
SWCLK: D3.1 (A1), J4.9, U11.24 (SWCLK)
SWDATA: D21.1 (A1), J4.10, U11.25 (SWD)
TEMP_SENSE_0: C97.1, R88.2, U9.1 (A4)
TEMP_SENSE_1: C96.1, R87.2, U9.14 (A1)
UART0_RX: D12.2 (A2), R122.2, U11.28 (GPIO17)
UART0_TX: D13.2 (A2), R121.2, U11.27 (GPIO16)
UART1_RX: D11.2 (A2), R101.2, U11.32 (GPIO21)
UART1_TX: D9.2 (A2), R100.2, U11.31 (GPIO20)
USB_D+: R99.1, U11.47 (USB_DP)
USB_D-: R98.1, U11.46 (USB_DM)
VHIGH: R81.2; also elsewhere on the board
VLOW: R78.2; also elsewhere on the board

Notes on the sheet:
10uF-25V Ceramic Caps
Up to ~65V
CCM=0, DCM=0: Burst Mode CCM=0, DCM=1: Discontinuous Conduction Mode CCM=1, DCM=0: Forced Continuous Conduction Mode CCM=1, DCM=1: Forced Continuous Conduction Mode
Up to ~100V
